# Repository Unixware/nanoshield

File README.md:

**WTH is this...**

Shield/dock/whatever for [MiSTeryNano](https://github.com/harbaum/MiSTeryNano) project (nano tang 20k + M0S dock)  
Ports on this is just **MIDI-out** and **Joystick** only (no level shifters for mice)  
Resistors R1/R2 may need different values
100% THT so low cost to produce  

**WARNING**

YMMV _check_ before use, proceed with caution etc etc as I may have messed/missed something there...

**Thanks**

To [Till](https://github.com/harbaum/) for patiently answering my tech questions!

**BOM**

| ﻿Designator | Footprint                                                                                | Quantity | Value             |
| ------------- | ---------------------------------------------------------------------------------------- | -------- | ----------------- |
| C1            | C_Disc_D5.0mm_W2.5mm_P5.00mm                                                             | 1        | 100n              |
| J1, J3        | PinSocket_1x20_P2.54mm_Vertical                                                          | 2        | Conn_01x20_Socket |
| J2            | DSUB-9_Male_Horizontal_P2.77x2.84mm_EdgePinOffset7.70mm_Housed_MountingHolesOffset9.12mm | 1        | Joy               |
| J4            | PinSocket_2x06_P2.54mm_Horizontal                                                        | 1        | M0S               |
| J5            | MIDI_DIN5                                                                                | 1        | MIDI OUT          |
| R1, R2        | R_Axial_DIN0207_L6.3mm_D2.5mm_P10.16mm_Horizontal                                        | 2        | 100               |

R1/R2, C1 and MIDI (out) port not requred if you don't use MIDI

11/12/2025
Updated with fabrication files for [JLCPCB](https://jlcpcb.com/) 
nanoshield.zip as gerber file, bom.csv as BOM, positions.csv as CPL files (all of them into 'production' folder)
also note headers not visible on JLC's site - not big deal IMHO

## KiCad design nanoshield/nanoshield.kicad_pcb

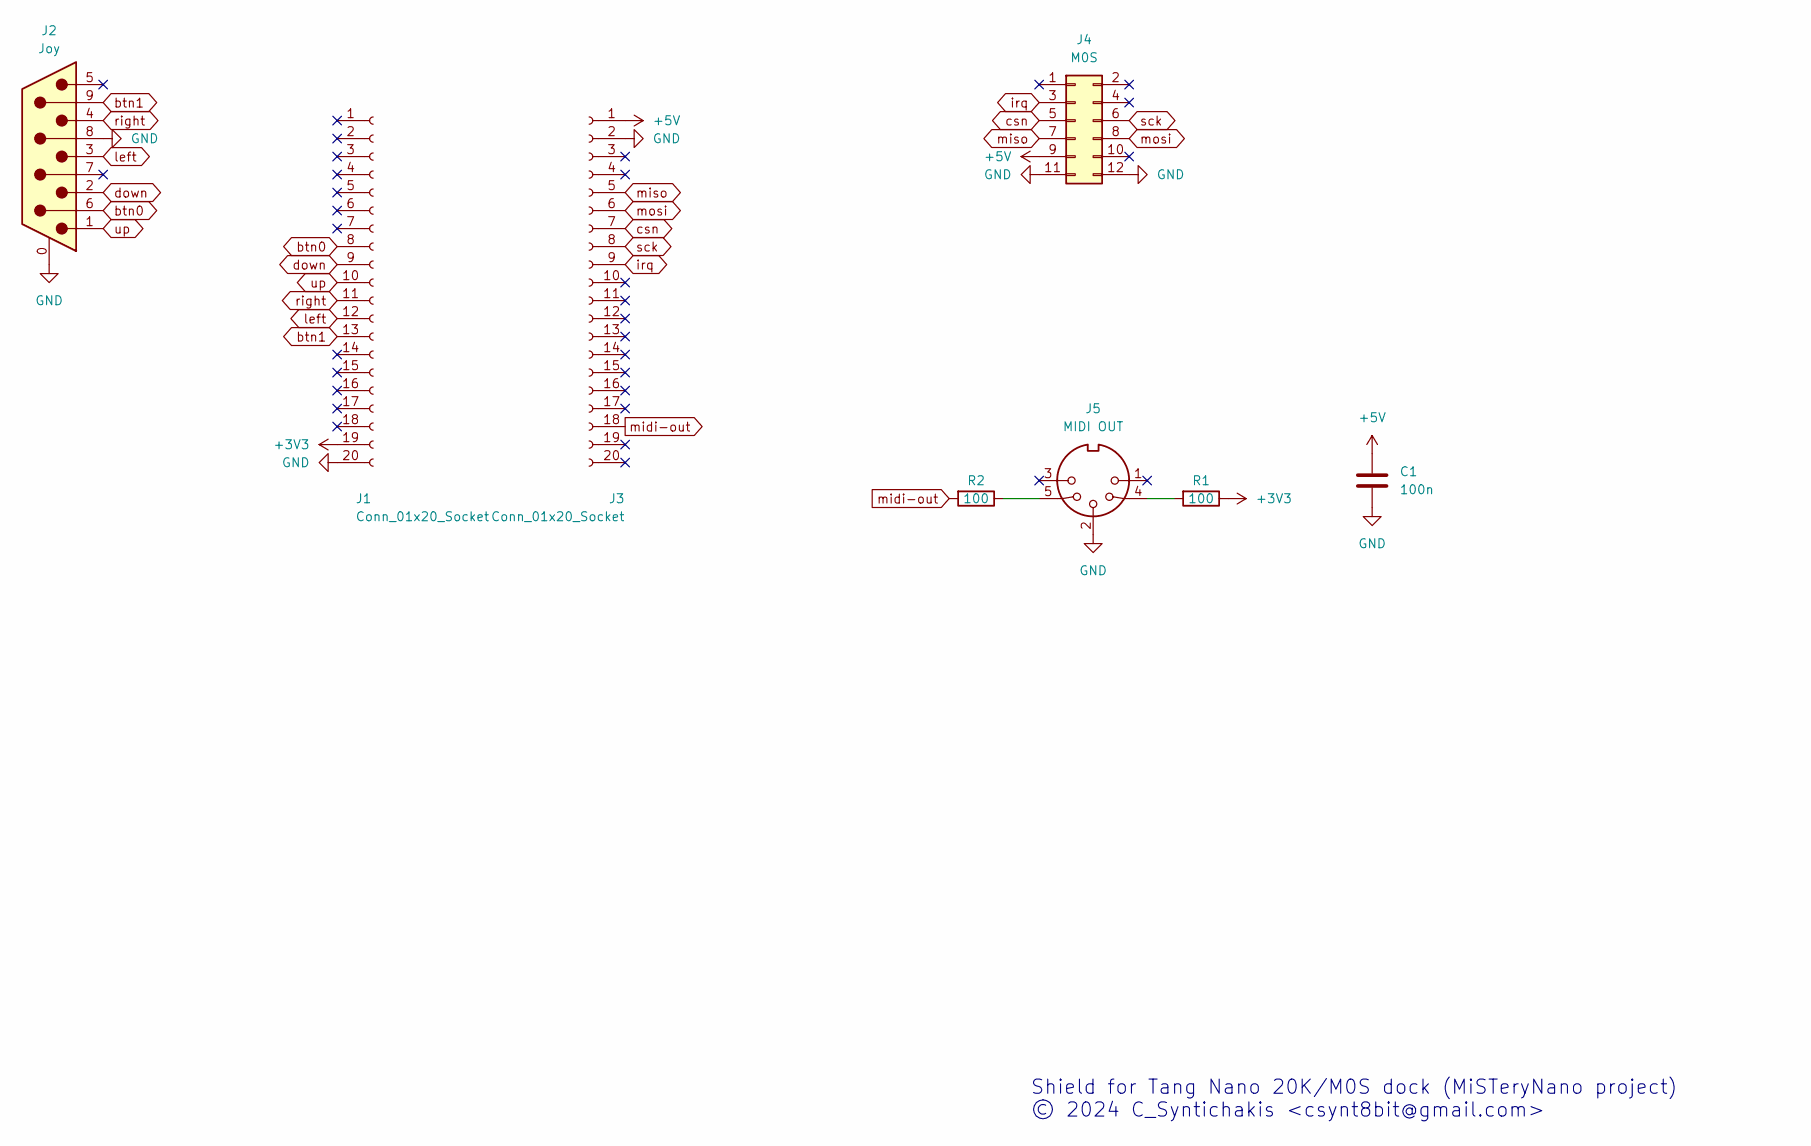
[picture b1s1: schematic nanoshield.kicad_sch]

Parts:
C1: 100n; C_Disc_D5.0mm_W2.5mm_P5.00mm; LCSC Part # C3009699
J1, J3: Conn_01x20_Socket; PinSocket_1x20_P2.54mm_Vertical; LCSC Part # C5224030
J2: Joy; DSUB-9_Male_Horizontal_P2.77x2.84mm_EdgePinOffset7.70mm_Hou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; LCSC Part # C141880
J4: M0S; PinSocket_2x06_P2.54mm_Horizontal; LCSC Part # C5333437
J5: MIDI OUT; MIDI_DIN5; LCSC Part # C2939346
R1, R2: 100; R_Axial_DIN0207_L6.3mm_D2.5mm_P10.16mm_Horizontal; LCSC Part # C1364269

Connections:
+3V3: J1.19, R1.1
+5V: C1.1, J3.1, J4.9
GND: C1.2, J1.20, J2.0 (PAD), J2.8, J3.2, J4.11, J4.12, J5.2
unnamed: J5.4, R1.2
unnamed: J5.5, R2.1
btn0: J1.8, J2.6
btn1: J1.13, J2.9
csn: J3.7, J4.5
down: J1.9, J2.2
irq: J3.9, J4.3
left: J1.12, J2.3
midi-out: J3.18, R2.2
miso: J3.5, J4.7
mosi: J3.6, J4.8
right: J1.11, J2.4
sck: J3.8, J4.6
up: J1.10, J2.1

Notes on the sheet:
Shield for Tang Nano 20K/M0S dock (MiSTeryNano project) © 2024 C_Syntichakis <csynt8bit@gmail.com>

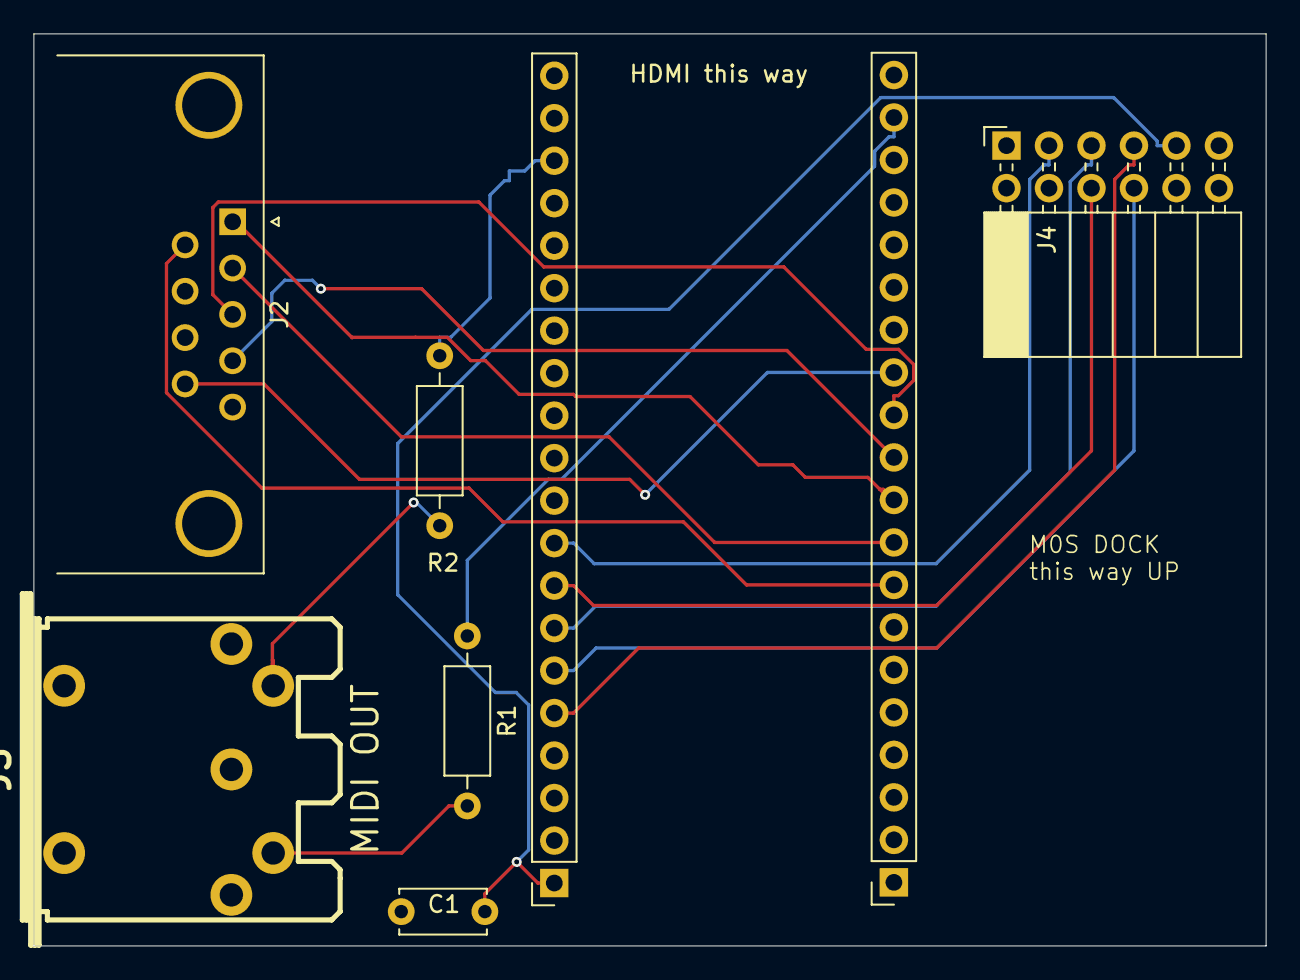
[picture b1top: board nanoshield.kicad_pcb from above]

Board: 2 copper layers, 73.7 x 54.5 mm, 8 parts (0 on the bottom side), 17 nets.

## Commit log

2025-12-11 added jlcpcb bom
2025-12-11 bom fix
2025-12-11 bom fix again
2025-12-11 Update README with fabrication files for JLCPCB
    Added fabrication files and notes for JLCPCB.
2025-12-11 Update README with fabrication files details
    Consolidate and clarify fabrication files update.
2025-12-13 Revise BOM details
    Updated BOM section with detailed component information
